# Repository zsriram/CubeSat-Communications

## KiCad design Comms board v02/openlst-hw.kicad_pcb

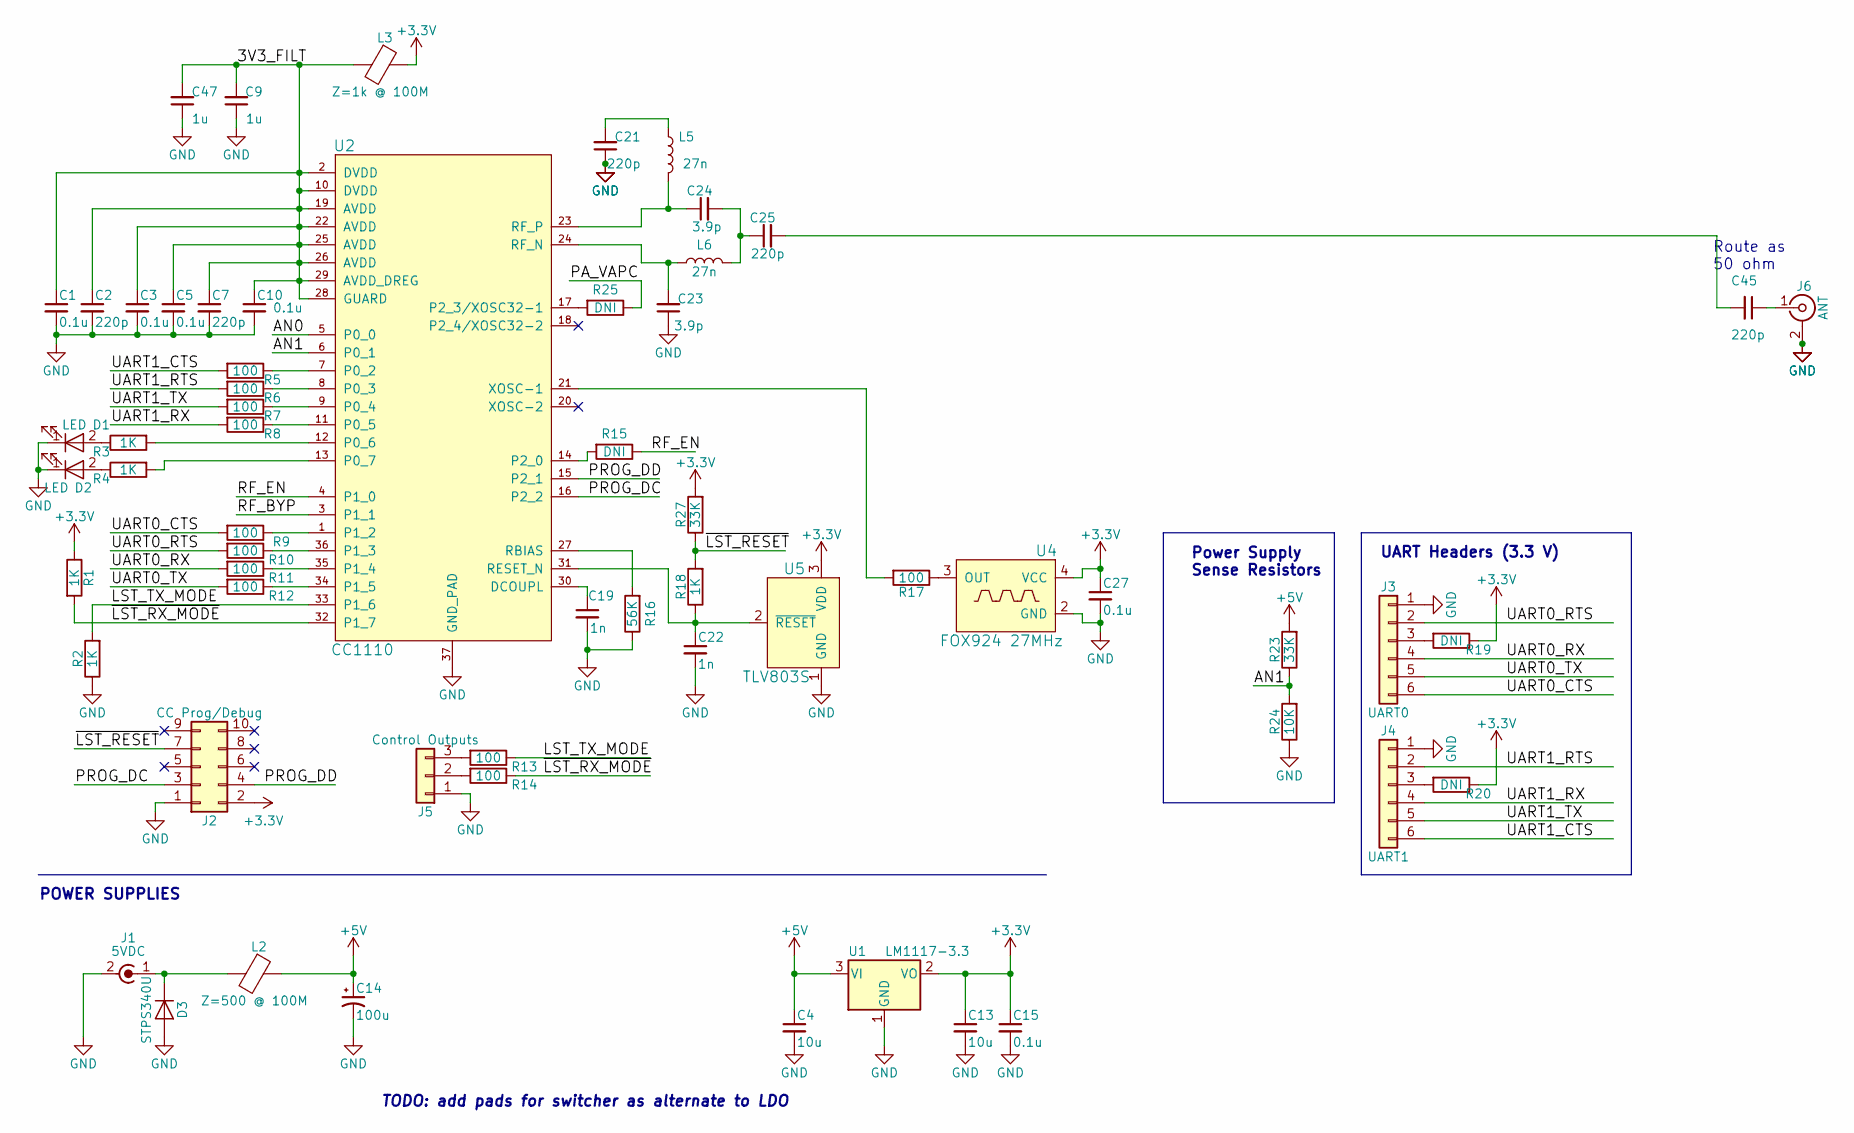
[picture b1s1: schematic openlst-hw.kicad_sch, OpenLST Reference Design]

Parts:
C1, C3, C5, C10, C15, C27: 0.1u; C_0603_1608Metric; ManufPN 0603YC104K4T4A
C2, C7, C21, C25, C45: 220p; C_0402_1005Metric; ManufPN C0402C221J2GACAUTO
C4, C13: 10u; C_0603_1608Metric; ManufPN GRT188C81A106ME13D
C9, C47: 1u; C_0603_1608Metric; ManufPN CL10B105MO8NNWC
C14: 100u; CP_EIA-3528-15_AVX-H; ManufPN TPSB107M010R0400
C19, C22: 1n; C_0603_1608Metric; ManufPN GCM188R71E102KA37D
C23, C24: 3.9p; C_0402_1005Metric; ManufPN GJM1555C1H3R9CB01D
D1: LED; LED_0603_1608Metric; ManufPN 150060VS75000
D2: LED; LED_0603_1608Metric; ManufPN 150060SS75000
D3: STPS340U; D_SMB; ManufPN STPS340U
J1: 5VDC; PinHeader_1x02_P2.54mm_Vertical
J2: CC Prog/Debug; PinHeader_2x05_P1.27mm_Vertical_SMD; ManufPN FTSH-105-01-L-DV-K-P
J3: UART0; PinHeader_1x06_P2.54mm_Vertical; ManufPN 61300611121
J4: UART1; PinHeader_1x06_P2.54mm_Vertical; ManufPN 61300611121
J5: Control Outputs; PinHeader_1x03_P2.54mm_Vertical
J6: ANT; SMA_Molex_73251-1153_EdgeMount_Horizontal; ManufPN 732511150
L2: Z=500 @ 100M; L_1206_3216Metric; ManufPN MI1206L501R-10
L3: Z=1k @ 100M; L_0603_1608Metric; ManufPN 74279266
L5, L6: 27n; L_0402_1005Metric; ManufPN LQW15AN27NJ00D
R1, R2, R3, R4, R18: 1K; R_0603_1608Metric; ManufPN RC0603JR-071KL
R5, R6, R7, R8, R9, R10, R11, R12, R13, R14, R17: 100; R_0603_1608Metric; ManufPN AC0603FR-07100RL
R15, R19, R20, R25: DNI; R_0603_1608Metric
R16: 56K; R_0603_1608Metric; ManufPN RMCF0603FT56K0
R23, R27: 33K; R_0603_1608Metric; ManufPN AC0603FR-0733KL
R24: 10K; R_0603_1608Metric; ManufPN RC0603JR-0710KL
U1: LM1117-3.3; SOT-223-3_TabPin2; ManufPN LM1117IMP-3.3/NOPB
U2: CC1110; TI_CC_QFN36; ManufPN CC1110F32RHHR
U4: FOX924 27MHz; Oscillator_SMD_Fordahl_DFAS15-4Pin_5.0x3.2mm; ManufPN FT5HNBPK27.0-T1
U5: TLV803S; SOT-23; ManufPN TLV803SDBZR

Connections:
+3V3: C13.1, C15.1, C27.1, J2.2, L3.1, R1.1, R19.1, R20.1, R27.2, U1.2 (VO), U4.4 (VCC), U5.3 (VDD)
+5V: C4.1, C14.1, L2.1, R23.2, U1.3 (VI)
/3V3_FILT: C1.1, C2.1, C3.1, C5.1, C7.1, C9.2, C10.1, C47.2, L3.2, U2.2 (DVDD), U2.10 (DVDD), U2.19 (AVDD), U2.22 (AVDD), U2.25 (AVDD), U2.26 (AVDD), U2.28 (GUARD), U2.29 (AVDD_DREG)
/AN0: U2.5 (P0_0)
/AN1: R23.1, R24.2, U2.6 (P0_1)
/LST_TX_MODE: R2.2, R13.1, U2.33 (P1_6)
/PA_VAPC: R25.1
/PROG_DC: J2.3, U2.16 (P2_2)
/PROG_DD: J2.4, U2.15 (P2_1)
/RF_BYP: U2.3 (P1_1)
/RF_EN: R15.1, U2.4 (P1_0)
/UART0_CTS: J3.6, R9.2
/UART0_RTS: J3.2, R10.2
/UART0_RX: J3.4, R11.2
/UART0_TX: J3.5, R12.2
/UART1_CTS: J4.6, R5.2
/UART1_RTS: J4.2, R6.2
/UART1_RX: J4.4, R8.2
/UART1_TX: J4.5, R7.2
/~LST_RESET: J2.7, R18.2, R27.1
/~LST_RX_MODE: R1.2, R14.1, U2.32 (P1_7)
GND: C1.2, C2.2, C3.2, C4.2, C5.2, C7.2, C9.1, C10.2, C13.2, C14.2, C15.2, C19.2, C21.1, C22.2, C23.1, C27.2, C47.1, D1.1 (K), D2.1 (K), D3.2 (A), J1.2 (Ext), J2.1, J3.1, J4.1, J5.1, J6.2 (Ext), R2.1, R16.1, R24.1, U1.1 (GND), U2.37 (GND_PAD), U4.2 (GND), U5.1 (GND)
unnamed: C19.1, U2.30 (DCOUPL)
unnamed: C21.2, L5.1
unnamed: C22.1, R18.1, U2.31 (RESET_N), U5.2 (~RESET)
unnamed: C23.2, L6.1, U2.24 (RF_N)
unnamed: C24.1, L5.2, U2.23 (RF_P)
unnamed: C24.2, C25.1, L6.2
unnamed: C25.2, C45.2
unnamed: C45.1, J6.1 (In)
unnamed: D1.2 (A), R3.1
unnamed: D2.2 (A), R4.1
unnamed: D3.1 (K), J1.1 (In), L2.2
unnamed: J3.3, R19.2
unnamed: J4.3, R20.2
unnamed: J5.2, R14.2
unnamed: J5.3, R13.2
unnamed: R3.2, U2.12 (P0_6)
unnamed: R4.2, U2.13 (P0_7)
unnamed: R5.1, U2.7 (P0_2)
unnamed: R6.1, U2.8 (P0_3)
unnamed: R7.1, U2.9 (P0_4)
unnamed: R8.1, U2.11 (P0_5)
unnamed: R9.1, U2.1 (P1_2)
unnamed: R10.1, U2.36 (P1_3)
unnamed: R11.1, U2.35 (P1_4)
unnamed: R12.1, U2.34 (P1_5)
unnamed: R15.2, U2.14 (P2_0)
unnamed: R16.2, U2.27 (RBIAS)
unnamed: R17.1, U4.3 (OUT)
unnamed: R17.2, U2.21 (XOSC-1)
unnamed: R25.2, U2.17 (P2_3/XOSC32-1)

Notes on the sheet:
Route as 50 ohm
Power Supply Sense Resistors
UART Headers (3.3 V)
POWER SUPPLIES
TODO: add pads for switcher as alternate to LDO

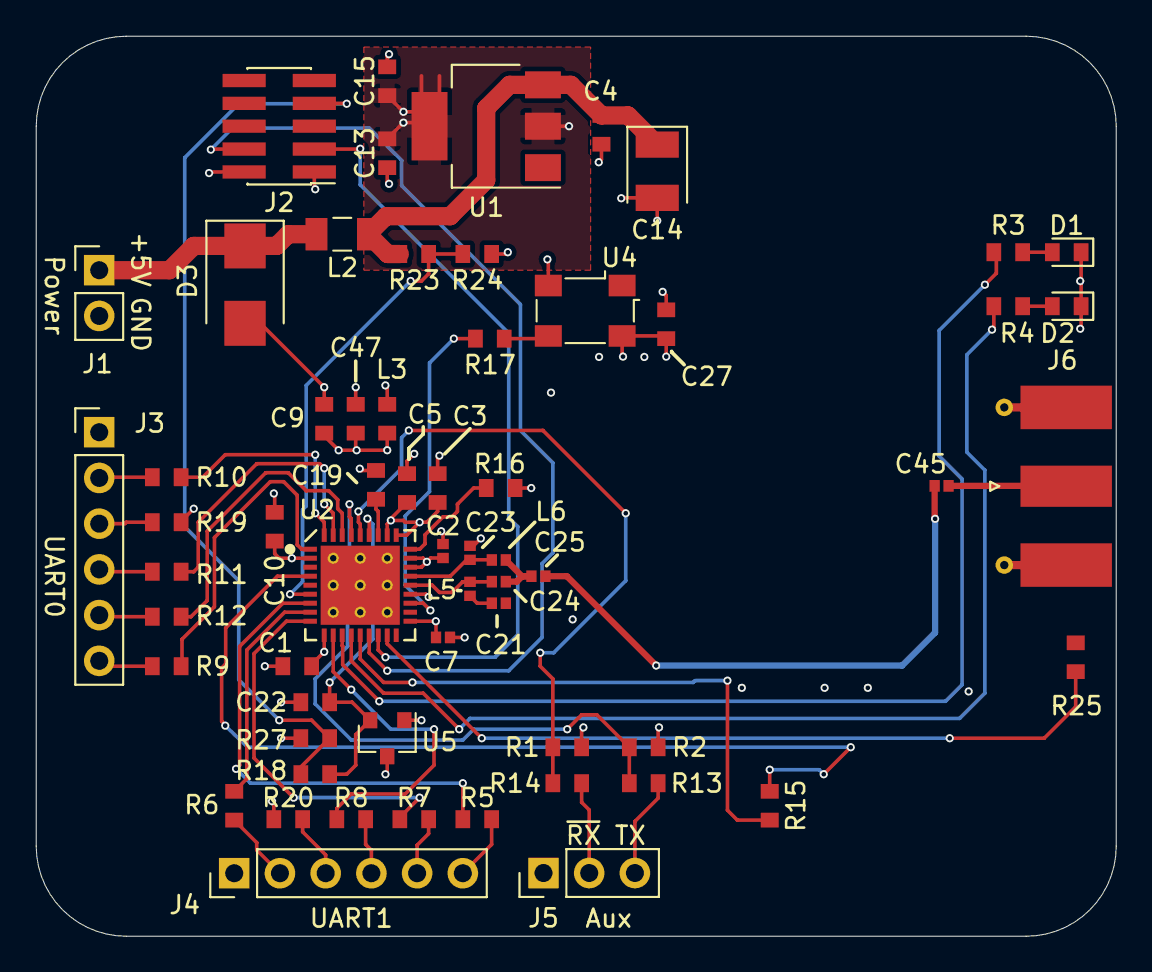
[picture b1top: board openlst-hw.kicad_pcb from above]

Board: 4 copper layers, 60.0 x 50.0 mm, 61 parts (0 on the bottom side), 49 nets.

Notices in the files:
Comms board v02/openlst-hw.kicad_pcb:
This work is licensed under a
Creative Commons Attribution-ShareAlike 4.0
International License (CC-BY-SA 4.0).
Comms board v02/openlst-hw.kicad_sch:
This work is licensed under a Creative Commons Attribution-ShareAlike 4.0 International
Copyright 2018 Planet Labs Inc
